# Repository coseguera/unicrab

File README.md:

# unicrab
A keyboard inspired in the Ferris Sweep but not split. It has choc spacing

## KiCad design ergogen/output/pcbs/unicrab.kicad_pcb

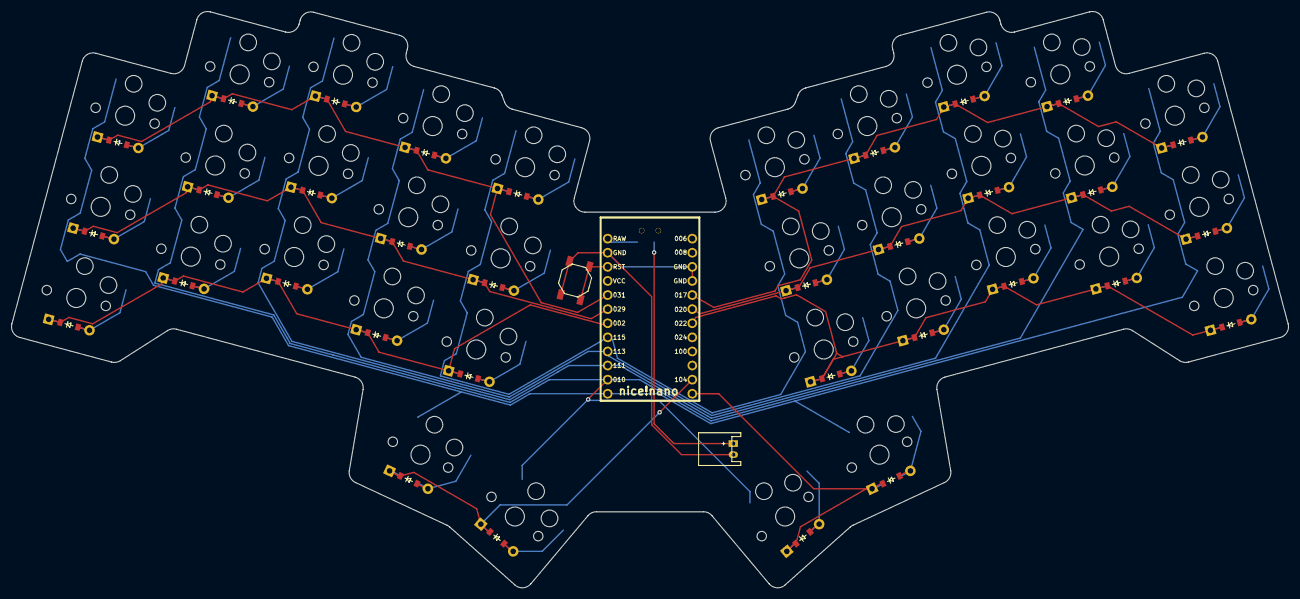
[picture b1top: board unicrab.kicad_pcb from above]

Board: 2 copper layers, 230.0 x 103.8 mm, 72 parts (0 on the bottom side), 51 nets.

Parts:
B1: SW_TACT_ALPS_SKQGABE010
D1, D2, D3, D4, D5, D6, D7, D8, D9, D10, D11, D12, D13, D14, D15, D16, D17, D18, D19, D20, D21, D22, D23, D24, D25, D26, D27, D28, D29, D30, D31, D32, D33, D34: ComboDiode
JST1: JST_PH_S2B-PH-K_02x2.00mm_Angled
MCU1: nice_nano
S1, S2, S3, S4, S5, S6, S7, S8, S9, S10, S11, S12, S13, S14, S15, S16, S17, S18, S19, S20, S21, S22, S23, S24, S25, S26, S27, S28, S29, S30, S31, S32, S33, S34: PG1350
T1: SPDT_C128955

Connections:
GND: B1.1, JST1.2, MCU1.3, MCU1.4, MCU1.23
P002: D1.1, D4.1, D7.1, D10.1, D13.1, MCU1.18
P009: MCU1.13, S1.1, S2.1, S3.1, S16.1, S18.1, S19.1, S20.1, S33.1
P010: MCU1.14, S4.1, S5.1, S6.1, S17.1, S21.1, S22.1, S23.1, S34.1
P017: D20.1, D23.1, D26.1, D29.1, D32.1, MCU1.5
P020: D19.1, D22.1, D25.1, D28.1, D31.1, MCU1.6
P022: D18.1, D21.1, D24.1, D27.1, D30.1, MCU1.7
P029: D2.1, D5.1, D8.1, D11.1, D14.1, MCU1.19
P031: D3.1, D6.1, D9.1, D12.1, D15.1, MCU1.20
P104: D16.1, D17.1, MCU1.11
P106: D33.1, D34.1, MCU1.12
P111: MCU1.15, S7.1, S8.1, S9.1, S24.1, S25.1, S26.1
P113: MCU1.16, S10.1, S11.1, S12.1, S27.1, S28.1, S29.1
P115: MCU1.17, S13.1, S14.1, S15.1, S30.1, S31.1, S32.1
RAW: MCU1.24, T1.1
RST: B1.2, MCU1.22
index_bottom: D10.2, S10.2
index_home: D11.2, S11.2
index_top: D12.2, S12.2
inner_bottom: D13.2, S13.2
inner_home: D14.2, S14.2
inner_top: D15.2, S15.2
middle_bottom: D7.2, S7.2
middle_home: D8.2, S8.2
middle_top: D9.2, S9.2
mirror_index_bottom: D27.2, S27.2
mirror_index_home: D28.2, S28.2
mirror_index_top: D29.2, S29.2
mirror_inner_bottom: D30.2, S30.2
mirror_inner_home: D31.2, S31.2
mirror_inner_top: D32.2, S32.2
mirror_middle_bottom: D24.2, S24.2
mirror_middle_home: D25.2, S25.2
mirror_middle_top: D26.2, S26.2
mirror_pinky_bottom: D18.2, S18.2
mirror_pinky_home: D19.2, S19.2
mirror_pinky_top: D20.2, S20.2
mirror_reachy_cluster: D34.2, S34.2
mirror_ring_bottom: D21.2, S21.2
mirror_ring_home: D22.2, S22.2
mirror_ring_top: D23.2, S23.2
mirror_tucky_cluster: D33.2, S33.2
pinky_bottom: D1.2, S1.2
pinky_home: D2.2, S2.2
pinky_top: D3.2, S3.2
pos: JST1.1, T1.2
reachy_cluster: D17.2, S17.2
ring_bottom: D4.2, S4.2
ring_home: D5.2, S5.2
ring_top: D6.2, S6.2
tucky_cluster: D16.2, S16.2

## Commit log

2024-07-27 add the board with a nice_nano
2024-07-27 add reset switch footprint
2024-07-28 add the rest of the components
2024-07-28 add the generated output
2024-07-29 remove the footprint we are not using
2024-07-29 move the switch to the top and back
2024-07-29 position the controller at the edge of the board
2024-07-29 place the reset button
2024-07-29 place the jstph
2024-07-29 adjust the top side of the controller
2024-07-29 rotate the reset button
2024-07-29 invert the slider
2024-07-29 add more edges
2024-07-29 uncomment nice nano
2024-07-29 update the kicad file
2024-07-29 add the pad to diode connections
2024-07-29 connect rows and columns
2024-07-29 add reset and switch connection
2024-07-29 connect the rows
2024-07-29 connect the battery
2024-07-30 finish connectionx
2024-07-30 add other output files
2024-07-30 reset mask clearance
2024-07-30 rearrange controller connections
2024-07-30 swap top and home
2024-07-30 wire the left side
2024-07-30 wire middle components
2024-07-30 wire the rest
2024-07-30 add the rest of the output files
